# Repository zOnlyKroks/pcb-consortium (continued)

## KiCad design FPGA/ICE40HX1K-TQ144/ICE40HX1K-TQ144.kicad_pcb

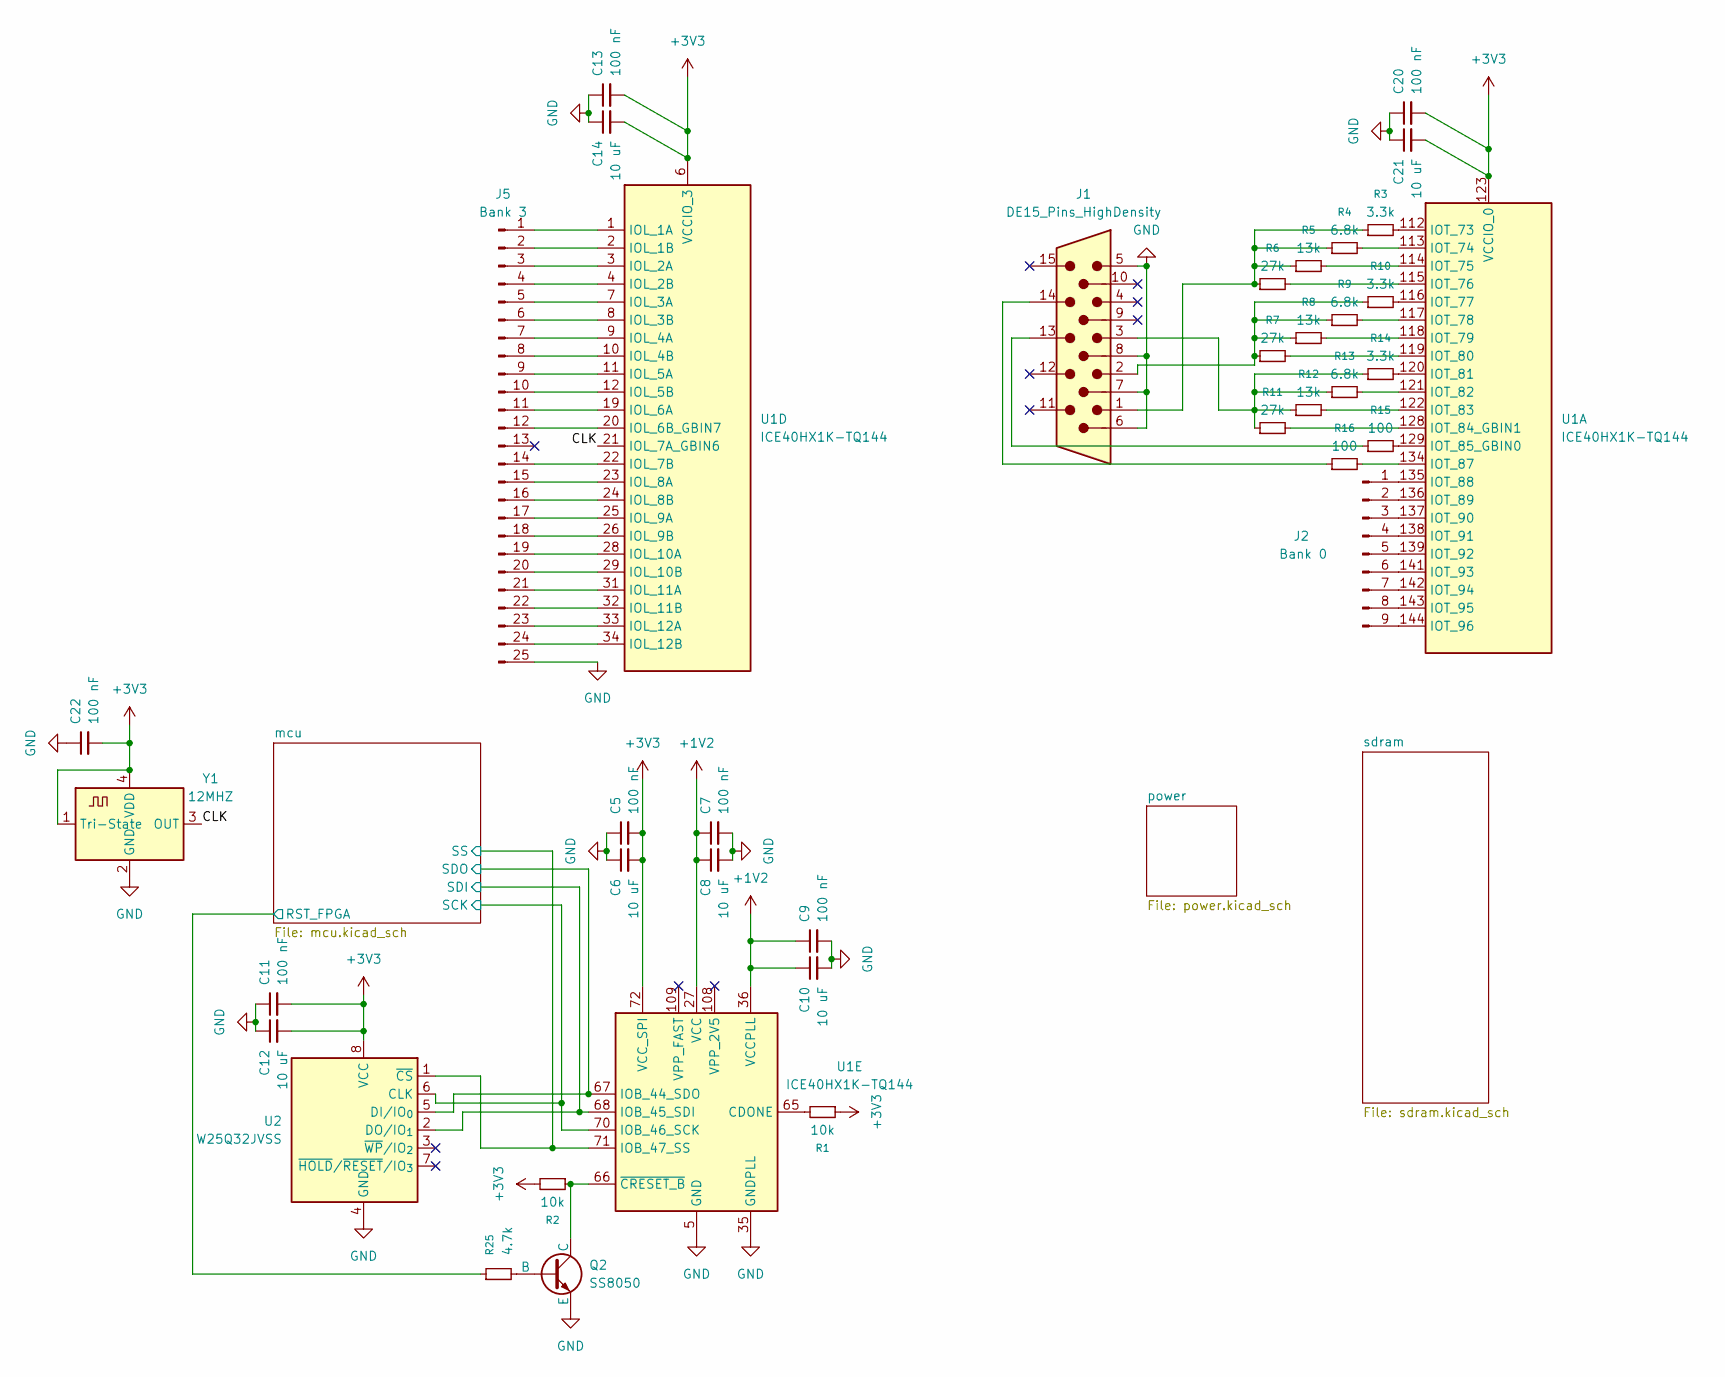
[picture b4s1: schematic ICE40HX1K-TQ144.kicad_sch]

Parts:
C5, C7, C9, C11, C13, C20, C22: 100 nF; C_0603_1608Metric
C6, C8, C10, C12, C14, C21: 10 uF; C_0603_1608Metric
J1: DE15_Pins_HighDensity; DSUB-15-HD_Pins_Horizontal_P2.29x1.90mm_EdgePinOffset3.03mm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
J2: Bank 0; PinHeader_1x09_P2.54mm_Vertical
J5: Bank 3; PinHeader_1x25_P2.54mm_Vertical
Q2: SS8050; SOT-23
R1, R2: 10k; R_0603_1608Metric
R3, R10, R14: 3.3k; R_0603_1608Metric
R4, R9, R13: 6.8k; R_0603_1608Metric
R5, R8, R12: 13k; R_0603_1608Metric
R6, R7, R11: 27k; R_0603_1608Metric
R15, R16: 100; R_0603_1608Metric
R25: 4.7k; R_0603_1608Metric; LCSC Part # C23162
U1: ICE40HX1K-TQ144; TQFP-144_20x20mm_P0.5mm
U2: W25Q32JVSS; SOIC-8_5.3x5.3mm_P1.27mm
Y1: 12MHZ; Crystal_SMD_3225-4Pin_3.2x2.5mm; LCSC Part # C2901561

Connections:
+1V2: C7.1, C8.1, C9.1, C10.1, U1.27 (VCC), U1.36 (VCCPLL), U1.51 (VCC), U1.92 (VCC), U1.111 (VCC); also elsewhere on the board
+3V3: C5.2, C6.2, C11.2, C12.2, C13.2, C14.2, C20.2, C21.2, C22.2, R1.1, R2.2, U1.6 (VCCIO_3), U1.30 (VCCIO_3), U1.72 (VCC_SPI), U1.123 (VCCIO_0), U1.133 (VCCIO_0), U2.8 (VCC), Y1.1 (Tri-State), Y1.4 (VDD); also elsewhere on the board
/CLK: U1.21 (IOL_7A_GBIN6), Y1.3 (OUT)
/mcu/RST_FPGA: R25.1; also elsewhere on the board
/mcu/SCK: U1.70 (IOB_46_SCK), U2.6 (CLK); also elsewhere on the board
/mcu/SDI: U1.68 (IOB_45_SDI), U2.2 (DO/IO_{1}); also elsewhere on the board
/mcu/SDO: U1.67 (IOB_44_SDO), U2.5 (DI/IO_{0}); also elsewhere on the board
/mcu/SS: U1.71 (IOB_47_SS), U2.1 (~CS); also elsewhere on the board
GND: C5.1, C6.1, C7.2, C8.2, C9.2, C10.2, C11.1, C12.1, C13.1, C14.1, C20.1, C21.1, C22.1, J1.5, J1.6, J1.7, J1.8, J5.25, Q2.3 (E), U1.5 (GND), U1.13 (GND), U1.14 (GND), U1.35 (GNDPLL), U1.59 (GND), U1.69 (GND), U1.86 (GND), U1.103 (GND), U1.132 (GND), U1.140 (GND), U2.4 (GND), Y1.2 (GND); also elsewhere on the board
unnamed: J1.1, R3.1, R4.1, R5.1, R6.1
unnamed: J1.2, R7.1, R8.1, R9.1, R10.1
unnamed: J1.3, R11.1, R12.1, R13.1, R14.1
unnamed: J1.13, R15.1
unnamed: J1.14, R16.1
unnamed: J2.1, U1.135 (IOT_88)
unnamed: J2.2, U1.136 (IOT_89)
unnamed: J2.3, U1.137 (IOT_90)
unnamed: J2.4, U1.138 (IOT_91)
unnamed: J2.5, U1.139 (IOT_92)
unnamed: J2.6, U1.141 (IOT_93)
unnamed: J2.7, U1.142 (IOT_94)
unnamed: J2.8, U1.143 (IOT_95)
unnamed: J2.9, U1.144 (IOT_96)
unnamed: J5.1, U1.1 (IOL_1A)
unnamed: J5.2, U1.2 (IOL_1B)
unnamed: J5.3, U1.3 (IOL_2A)
unnamed: J5.4, U1.4 (IOL_2B)
unnamed: J5.5, U1.7 (IOL_3A)
unnamed: J5.6, U1.8 (IOL_3B)
unnamed: J5.7, U1.9 (IOL_4A)
unnamed: J5.8, U1.10 (IOL_4B)
unnamed: J5.9, U1.11 (IOL_5A)
unnamed: J5.10, U1.12 (IOL_5B)
unnamed: J5.11, U1.19 (IOL_6A)
unnamed: J5.12, U1.20 (IOL_6B_GBIN7)
unnamed: J5.14, U1.22 (IOL_7B)
unnamed: J5.15, U1.23 (IOL_8A)
unnamed: J5.16, U1.24 (IOL_8B)
unnamed: J5.17, U1.25 (IOL_9A)
unnamed: J5.18, U1.26 (IOL_9B)
unnamed: J5.19, U1.28 (IOL_10A)
unnamed: J5.20, U1.29 (IOL_10B)
unnamed: J5.21, U1.31 (IOL_11A)
unnamed: J5.22, U1.32 (IOL_11B)
unnamed: J5.23, U1.33 (IOL_12A)
unnamed: J5.24, U1.34 (IOL_12B)
unnamed: Q2.2 (B), R25.2
unnamed: Q2.1 (C), R2.1, U1.66 (~CRESET_B)
unnamed: R3.2, U1.112 (IOT_73)
unnamed: R4.2, U1.113 (IOT_74)
unnamed: R5.2, U1.114 (IOT_75)
unnamed: R6.2, U1.115 (IOT_76)
unnamed: R10.2, U1.116 (IOT_77)
unnamed: R9.2, U1.117 (IOT_78)
unnamed: R8.2, U1.118 (IOT_79)
unnamed: R7.2, U1.119 (IOT_80)
unnamed: R14.2, U1.120 (IOT_81)
unnamed: R13.2, U1.121 (IOT_82)
unnamed: R12.2, U1.122 (IOT_83)
unnamed: R11.2, U1.128 (IOT_84_GBIN1)
unnamed: R15.2, U1.129 (IOT_85_GBIN0)
unnamed: R16.2, U1.134 (IOT_87)
unnamed: R1.2, U1.65 (CDONE)

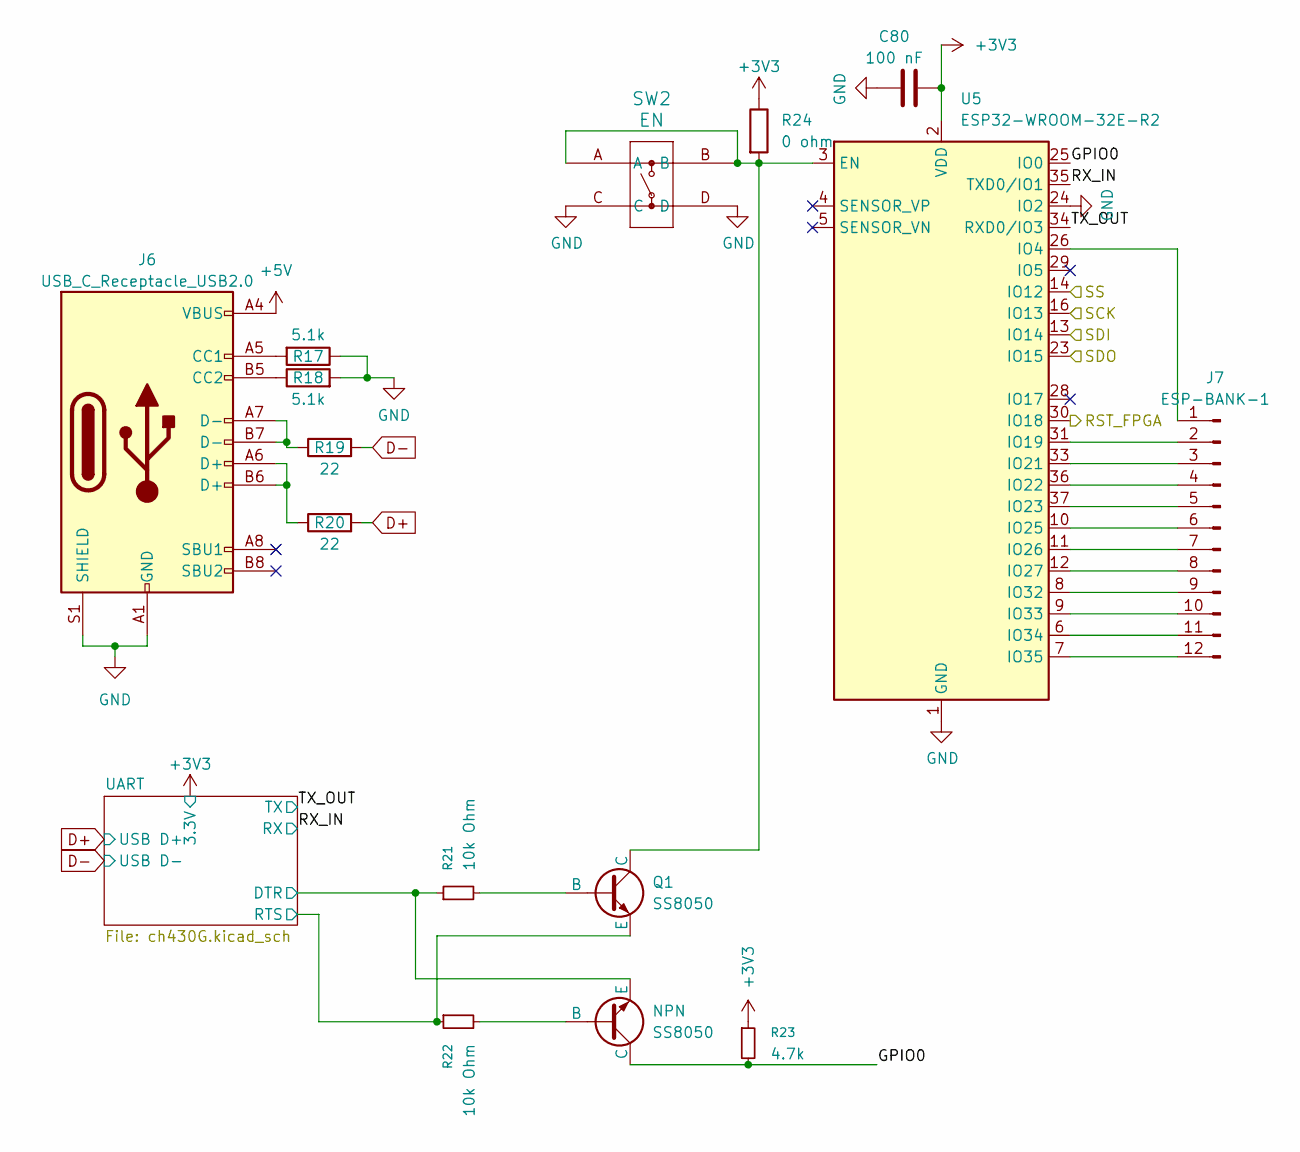
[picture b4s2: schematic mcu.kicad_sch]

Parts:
C80: 100 nF; C_0805_2012Metric; LCSC Part # C49678
J6: USB_C_Receptacle_USB2.0; USB_C_Receptacle_HRO_TYPE-C-31-M-12; JlcRotOffset 180
J7: ESP-BANK-1; PinHeader_1x12_P2.54mm_Vertical
Q1: SS8050; SOT-23
R17, R18: 5.1k; R_0805_2012Metric; LCSC Part # C27834
R19, R20: 22; R_0805_2012Metric; LCSC Part # C17561
R21, R22: 10k Ohm; R_0805_2012Metric
R23: 4.7k; R_0603_1608Metric; LCSC Part # C23162
R24: 0 ohm; R_0805_2012Metric; LCSC Part # C17477
SS8050: NPN; SOT-23
SW2: EN; KH-6X6X5H-STM_SKE; LCSC Part # C2837531
U5: ESP32-WROOM-32E-R2; ESP32-WROOM-32D

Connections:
+3V3: C80.1, R23.1, R24.1, U5.2 (VDD); also elsewhere on the board
+5V: J6.A4 (VBUS), J6.A9 (VBUS), J6.B4 (VBUS), J6.B9 (VBUS); also elsewhere on the board
/mcu/GPIO0: R23.2, SS8050.1 (C), U5.25 (IO0)
/mcu/RST_FPGA: U5.30 (IO18); also elsewhere on the board
/mcu/RX_IN: U5.35 (TXD0/IO1); also elsewhere on the board
/mcu/SCK: U5.16 (IO13); also elsewhere on the board
/mcu/SDI: U5.13 (IO14); also elsewhere on the board
/mcu/SDO: U5.23 (IO15); also elsewhere on the board
/mcu/SS: U5.14 (IO12); also elsewhere on the board
/mcu/TX_OUT: U5.34 (RXD0/IO3); also elsewhere on the board
/mcu/UART/DTR: R21.1, SS8050.3 (E); also elsewhere on the board
/mcu/UART/RTS: Q1.3 (E), R22.1; also elsewhere on the board
D+: R20.2; also elsewhere on the board
D-: R19.2; also elsewhere on the board
GND: C80.2, J6.A1 (GND), J6.A12 (GND), J6.B1 (GND), J6.B12 (GND), J6.S1 (SHIELD), R17.1, R18.2, SW2.C, SW2.D, U5.1 (GND), U5.15 (GND), U5.24 (IO2), U5.38 (GND), U5.39 (GND); also elsewhere on the board
unnamed: J6.A5 (CC1), R17.2
unnamed: J6.B5 (CC2), R18.1
unnamed: J6.A6 (D+), J6.B6 (D+), R20.1
unnamed: J6.A7 (D-), J6.B7 (D-), R19.1
unnamed: J7.1, U5.26 (IO4)
unnamed: J7.2, U5.31 (IO19)
unnamed: J7.3, U5.33 (IO21)
unnamed: J7.4, U5.36 (IO22)
unnamed: J7.5, U5.37 (IO23)
unnamed: J7.6, U5.10 (IO25)
unnamed: J7.7, U5.11 (IO26)
unnamed: J7.8, U5.12 (IO27)
unnamed: J7.9, U5.8 (IO32)
unnamed: J7.10, U5.9 (IO33)
unnamed: J7.11, U5.6 (IO34)
unnamed: J7.12, U5.7 (IO35)
unnamed: Q1.2 (B), R21.2
unnamed: Q1.1 (C), R24.2, SW2.A, SW2.B, U5.3 (EN)
unnamed: R22.2, SS8050.2 (B)

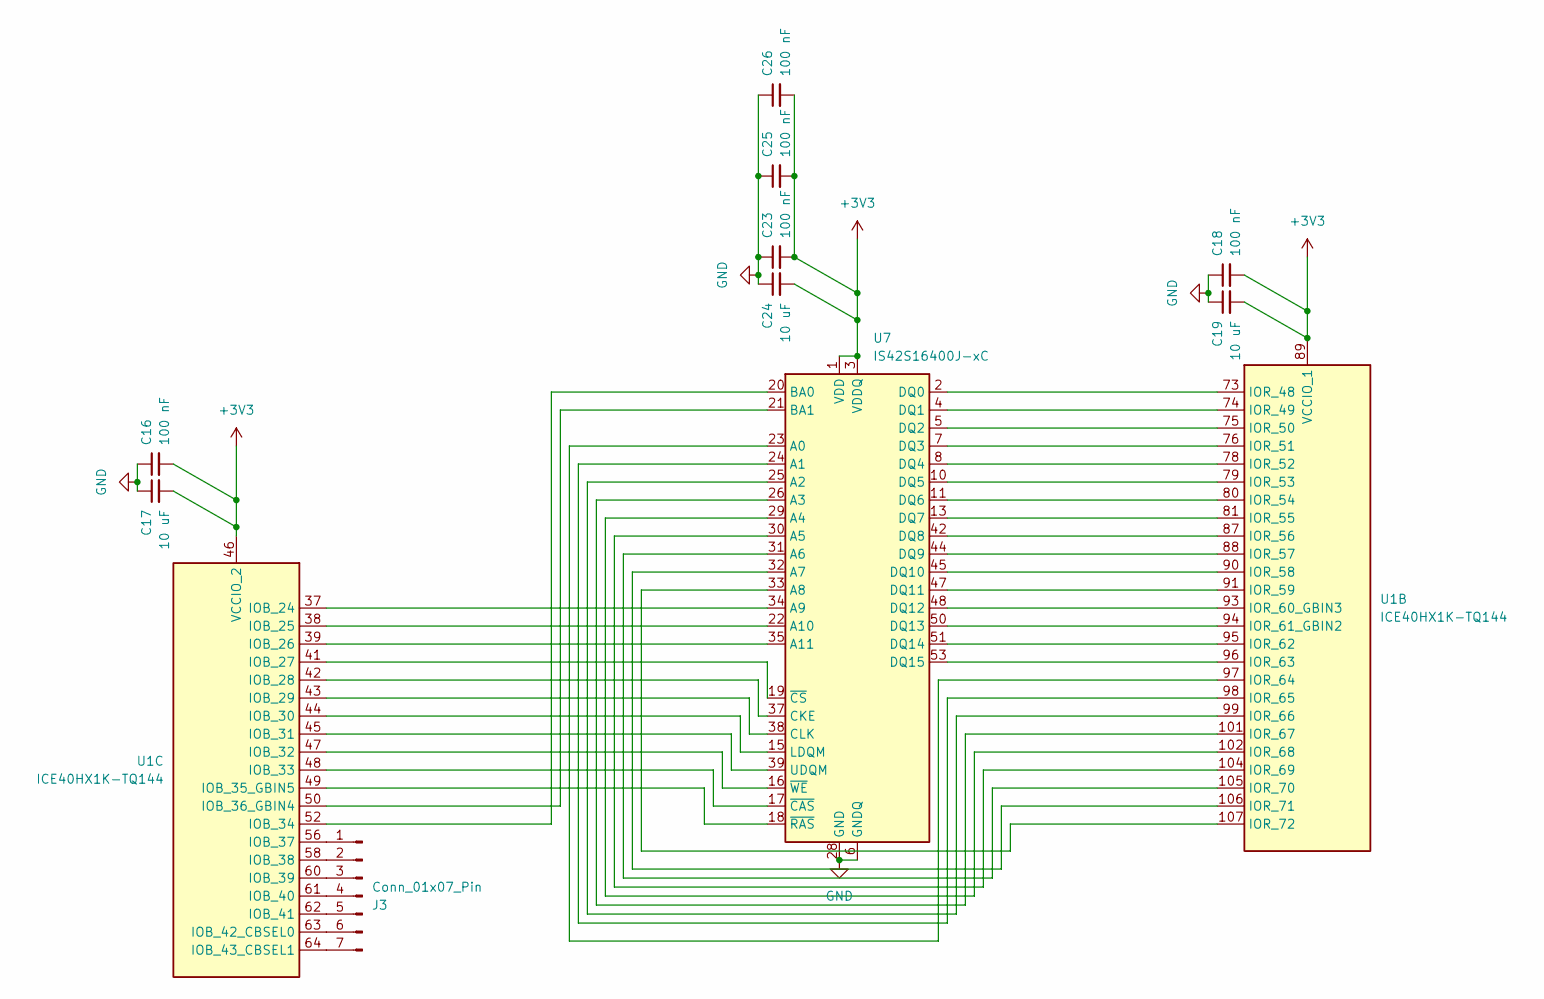
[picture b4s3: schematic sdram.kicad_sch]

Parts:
C16, C18, C23, C25, C26: 100 nF; C_0603_1608Metric
C17, C19, C24: 10 uF; C_0603_1608Metric
J3: Conn_01x07_Pin; PinHeader_1x07_P2.54mm_Vertical
U1: ICE40HX1K-TQ144; TQFP-144_20x20mm_P0.5mm
U7: IS42S16400J-xC; TSOP-II-54_22.2x10.16mm_P0.8mm

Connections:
+3V3: C16.2, C17.2, C18.2, C19.2, C23.2, C24.2, C25.2, C26.2, U1.46 (VCCIO_2), U1.57 (VCCIO_2), U1.89 (VCCIO_1), U1.100 (VCCIO_1), U7.1 (VDD), U7.3 (VDDQ), U7.9 (VDDQ), U7.14 (VDD), U7.27 (VDD), U7.43 (VDDQ), U7.49 (VDDQ); also elsewhere on the board
GND: C16.1, C17.1, C18.1, C19.1, C23.1, C24.1, C25.1, C26.1, U7.6 (GNDQ), U7.12 (GNDQ), U7.28 (GND), U7.41 (GND), U7.46 (GNDQ), U7.52 (GNDQ), U7.54 (GND); also elsewhere on the board
unnamed: J3.1, U1.56 (IOB_37)
unnamed: J3.2, U1.58 (IOB_38)
unnamed: J3.3, U1.60 (IOB_39)
unnamed: J3.4, U1.61 (IOB_40)
unnamed: J3.5, U1.62 (IOB_41)
unnamed: J3.6, U1.63 (IOB_42_CBSEL0)
unnamed: J3.7, U1.64 (IOB_43_CBSEL1)
unnamed: U1.73 (IOR_48), U7.2 (DQ0)
unnamed: U1.74 (IOR_49), U7.4 (DQ1)
unnamed: U1.75 (IOR_50), U7.5 (DQ2)
unnamed: U1.76 (IOR_51), U7.7 (DQ3)
unnamed: U1.78 (IOR_52), U7.8 (DQ4)
unnamed: U1.79 (IOR_53), U7.10 (DQ5)
unnamed: U1.80 (IOR_54), U7.11 (DQ6)
unnamed: U1.81 (IOR_55), U7.13 (DQ7)
unnamed: U1.87 (IOR_56), U7.42 (DQ8)
unnamed: U1.88 (IOR_57), U7.44 (DQ9)
unnamed: U1.90 (IOR_58), U7.45 (DQ10)
unnamed: U1.91 (IOR_59), U7.47 (DQ11)
unnamed: U1.93 (IOR_60_GBIN3), U7.48 (DQ12)
unnamed: U1.94 (IOR_61_GBIN2), U7.50 (DQ13)
unnamed: U1.95 (IOR_62), U7.51 (DQ14)
unnamed: U1.96 (IOR_63), U7.53 (DQ15)
unnamed: U1.97 (IOR_64), U7.23 (A0)
unnamed: U1.98 (IOR_65), U7.24 (A1)
unnamed: U1.99 (IOR_66), U7.25 (A2)
unnamed: U1.101 (IOR_67), U7.26 (A3)
unnamed: U1.102 (IOR_68), U7.29 (A4)
unnamed: U1.104 (IOR_69), U7.30 (A5)
unnamed: U1.105 (IOR_70), U7.31 (A6)
unnamed: U1.106 (IOR_71), U7.32 (A7)
unnamed: U1.107 (IOR_72), U7.33 (A8)
unnamed: U1.37 (IOB_24), U7.34 (A9)
unnamed: U1.38 (IOB_25), U7.22 (A10)
unnamed: U1.39 (IOB_26), U7.35 (A11)
unnamed: U1.41 (IOB_27), U7.19 (~CS)
unnamed: U1.42 (IOB_28), U7.37 (CKE)
unnamed: U1.43 (IOB_29), U7.38 (CLK)
unnamed: U1.44 (IOB_30), U7.15 (LDQM)
unnamed: U1.45 (IOB_31), U7.39 (UDQM)
unnamed: U1.47 (IOB_32), U7.16 (~WE)
unnamed: U1.48 (IOB_33), U7.17 (~CAS)
unnamed: U1.52 (IOB_34), U7.20 (BA0)
unnamed: U1.49 (IOB_35_GBIN5), U7.18 (~RAS)
unnamed: U1.50 (IOB_36_GBIN4), U7.21 (BA1)

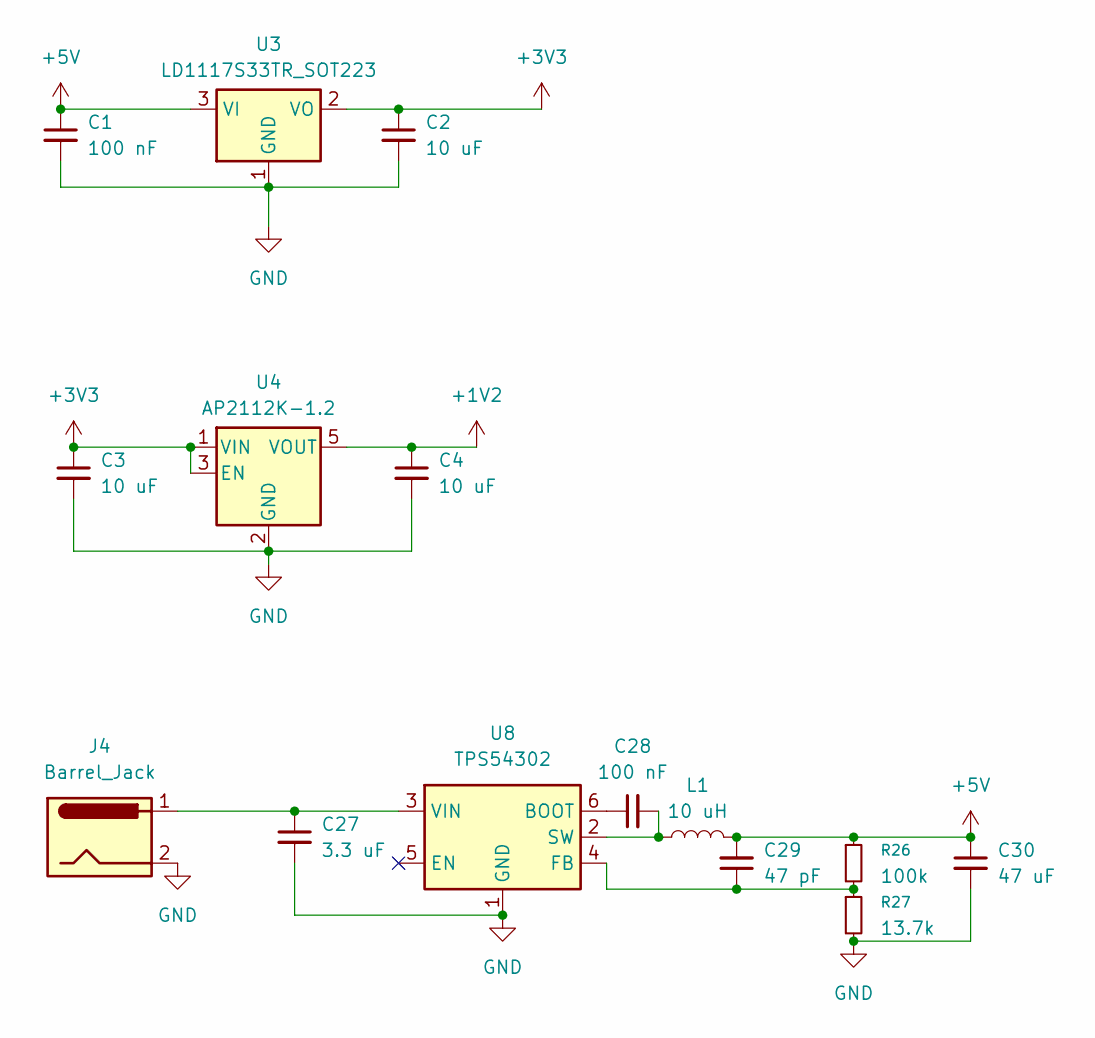
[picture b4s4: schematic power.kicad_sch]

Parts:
C1, C28: 100 nF; C_0603_1608Metric
C2, C3, C4: 10 uF; C_0603_1608Metric
C27: 3.3 uF; C_0603_1608Metric
C29: 47 pF; C_0603_1608Metric
C30: 47 uF; C_0603_1608Metric
J4: Barrel_Jack; BarrelJack_Horizontal
L1: 10 uH; L_0805_2012Metric
R26: 100k; R_0603_1608Metric
R27: 13.7k; R_0603_1608Metric
U3: LD1117S33TR_SOT223; SOT-223-3_TabPin2
U4: AP2112K-1.2; SOT-23-5
U8: TPS54302; SOT-23-6

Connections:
+1V2: C4.1, U4.5 (VOUT); also elsewhere on the board
+3V3: C2.1, C3.1, U3.2 (VO), U4.1 (VIN), U4.3 (EN); also elsewhere on the board
+5V: C1.1, C29.2, C30.1, L1.2, R26.1, U3.3 (VI); also elsewhere on the board
GND: C1.2, C2.2, C3.2, C4.2, C27.2, C30.2, J4.2, R27.2, U3.1 (GND), U4.2 (GND), U8.1 (GND); also elsewhere on the board
unnamed: C28.1, U8.6 (BOOT)
unnamed: C29.1, R26.2, R27.1, U8.4 (FB)
unnamed: C28.2, L1.1, U8.2 (SW)
unnamed: C27.1, J4.1, U8.3 (VIN)

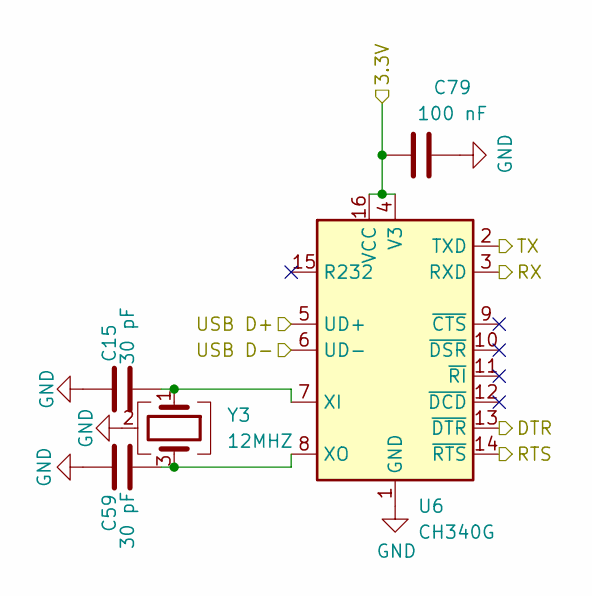
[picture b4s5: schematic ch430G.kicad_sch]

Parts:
C15, C59: 30 pF; C_0805_2012Metric; LCSC Part # C107108
C79: 100 nF; C_0805_2012Metric; LCSC Part # C49678
U6: CH340G; SOIC-16_3.9x9.9mm_P1.27mm
Y3: 12MHZ; Crystal_SMD_3225-4Pin_3.2x2.5mm; LCSC Part # C19631429

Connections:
+3V3: C79.2, U6.4 (V3), U6.16 (VCC); also elsewhere on the board
/mcu/RX_IN: U6.3 (RXD); also elsewhere on the board
/mcu/TX_OUT: U6.2 (TXD); also elsewhere on the board
/mcu/UART/DTR: U6.13 (~DTR); also elsewhere on the board
/mcu/UART/RTS: U6.14 (~RTS); also elsewhere on the board
D+: U6.5 (UD+); also elsewhere on the board
D-: U6.6 (UD-); also elsewhere on the board
GND: C15.1, C59.1, C79.1, U6.1 (GND), Y3.2 (G), Y3.4 (G); also elsewhere on the board
unnamed: C15.2, U6.7 (XI), Y3.1
unnamed: C59.2, U6.8 (XO), Y3.3

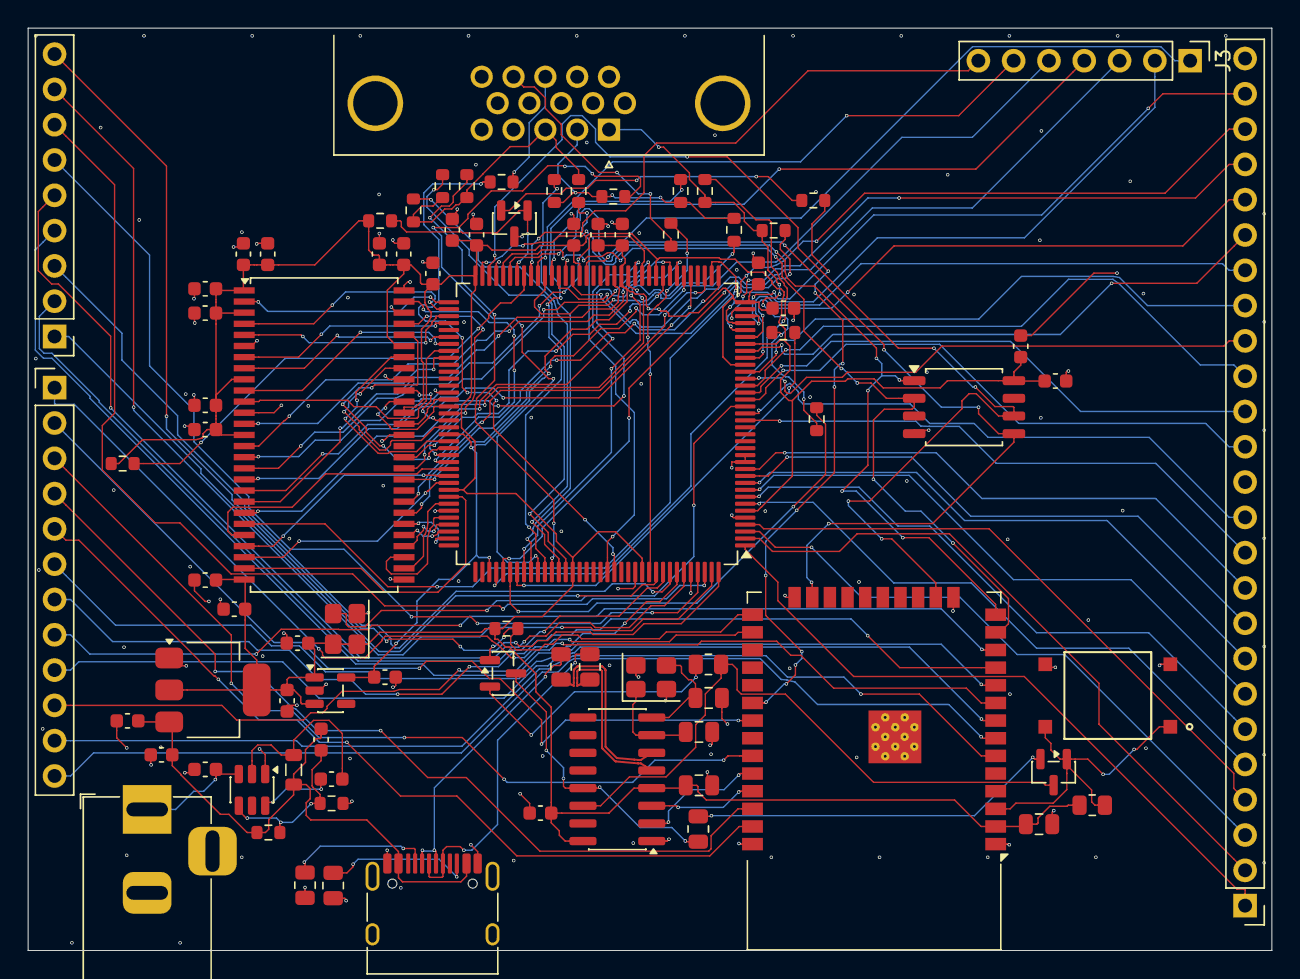
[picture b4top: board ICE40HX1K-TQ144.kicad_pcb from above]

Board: 4 copper layers, 89.5 x 66.4 mm, 82 parts (0 on the bottom side), 141 nets.

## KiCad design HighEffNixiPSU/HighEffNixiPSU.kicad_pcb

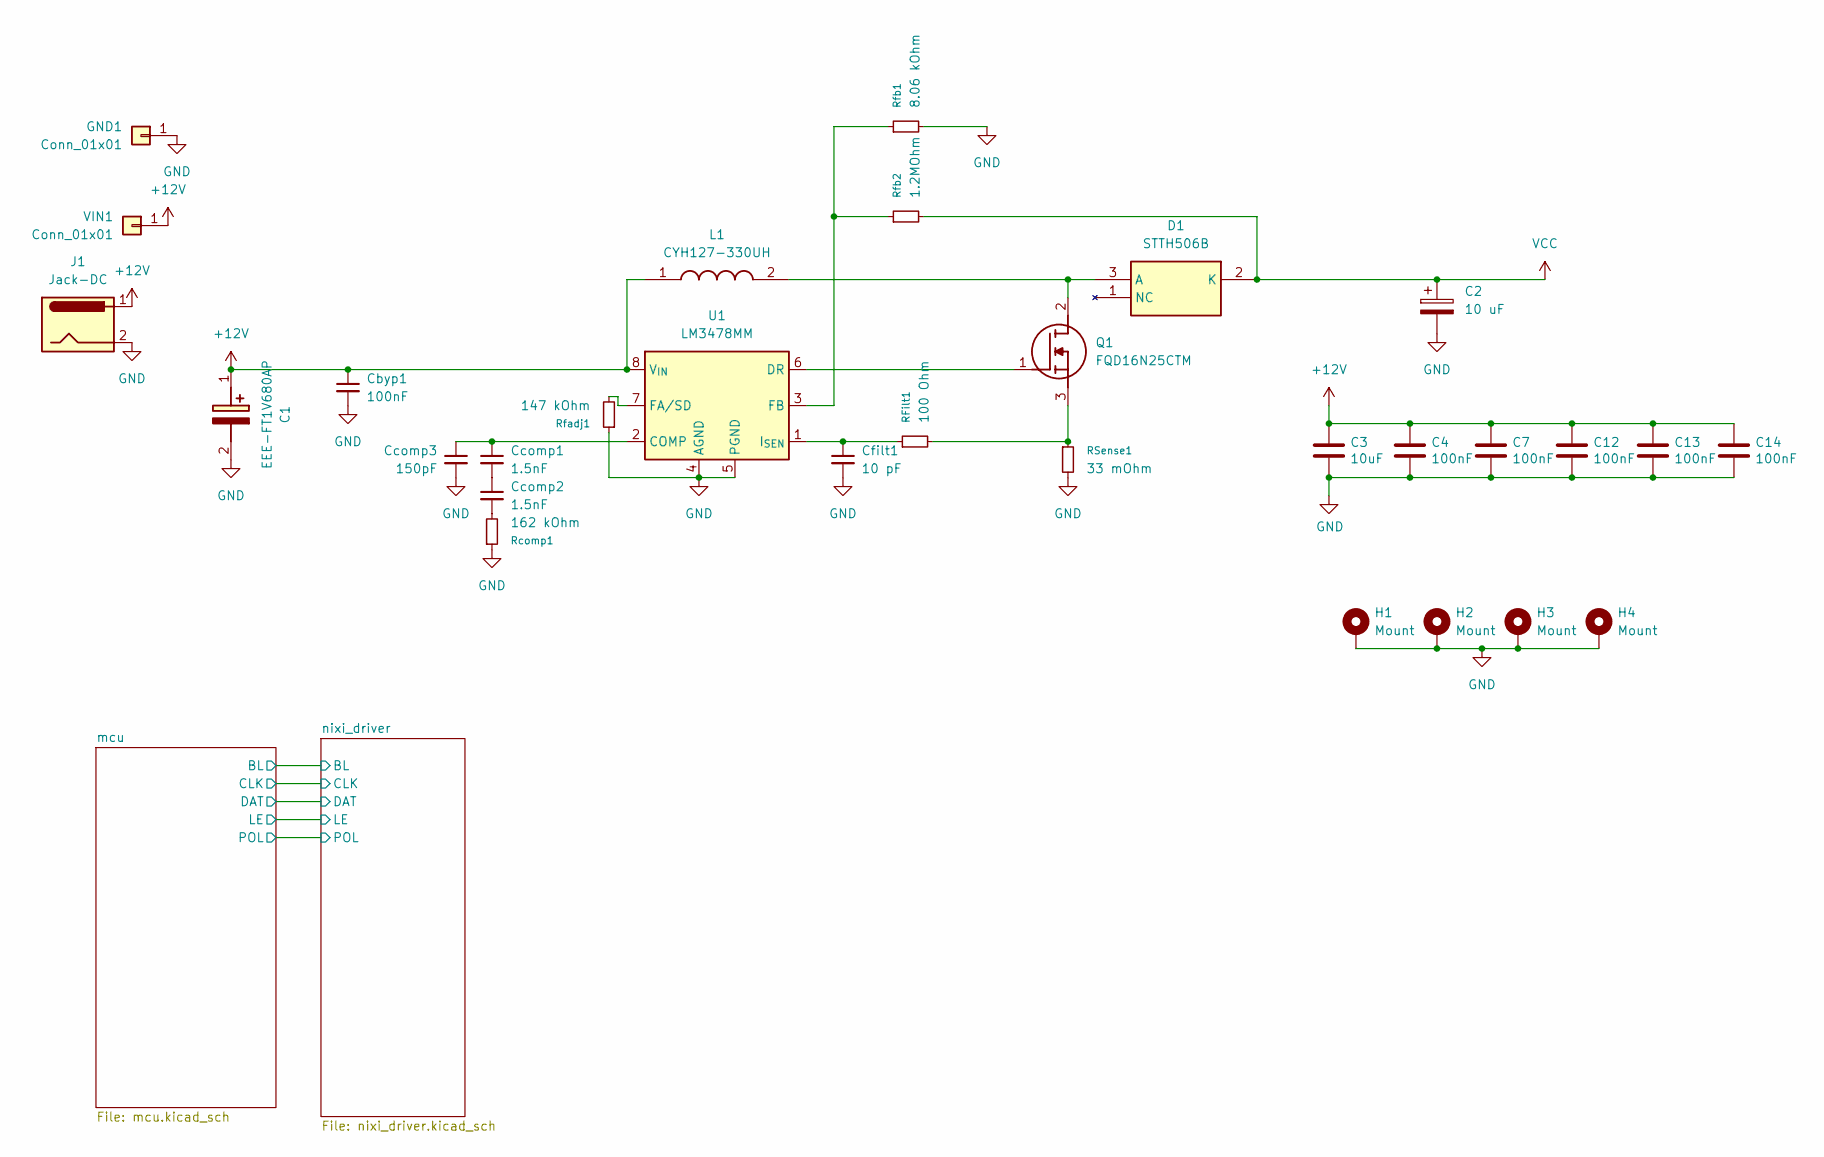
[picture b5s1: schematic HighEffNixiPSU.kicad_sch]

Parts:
C1: EEE-FT1V680AP; EEE1AA101SP; Mouser Part Number 667-EEE-FT1V680AP
C2: 10 uF; C_Elec_10x10.2; LCSC Part # C48970948
C3: 10uF; C_0805_2012Metric; LCSC C15850
C4, C7, C12, C13, C14: 100nF; C_0805_2012Metric; LCSC C28233
Cbyp1: 100nF; C_0805_2012Metric; LCSC Part # C784084
Ccomp1, Ccomp2: 1.5nF; C_0805_2012Metric; LCSC Part # C1717
Ccomp3: 150pF; C_0805_2012Metric; LCSC Part # C2168780
Cfilt1: 10 pF; C_0805_2012Metric; LCSC Part # C107107
D1: STTH506B; STTH506BTR; Mouser Part Number 511-STTH506B-TR
GND1: Conn_01x01; PinHeader_1x01_P2.54mm_Vertical; LCSC Part # C492400
H1, H2, H3, H4: Mount; MountingHole_3mm_Pad_TopOnly
J1: Jack-DC; BarrelJack_CUI_PJ-063AH_Horizontal; LCSC Part # C22434582
L1: CYH127-330UH; Mouser Part Number 652-SDR1307-331KL
Q1: FQD16N25CTM; Mouser Part Number 512-FQD16N25CTM
RFilt1: 100 Ohm; R_0805_2012Metric; LCSC Part # C17408
RSense1: 33 mOhm; R_1210_3225Metric; LCSC Part # C723419
Rcomp1: 162 kOhm; R_0805_2012Metric; LCSC Part # C47115899
Rfadj1: 147 kOhm; R_0805_2012Metric; LCSC Part # C47115874
Rfb1: 8.06 kOhm; R_0805_2012Metric; LCSC Part # C857074
Rfb2: 1.2MOhm; R_1206_3216Metric; LCSC Part # C36337
U1: LM3478MM; VSSOP-8_3x3mm_P0.65mm; LCSC Part # C9404
VIN1: Conn_01x01; PinHeader_1x01_P2.54mm_Vertical; LCSC Part # C492400

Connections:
+12V: C1.1 (+), C3.1, C4.1, C7.1, C12.1, C13.1, C14.1, Cbyp1.1, J1.1, L1.1, U1.8 (V_{IN}), VIN1.1; also elsewhere on the board
GND: C1.2 (-), C2.2, C3.2, C4.2, C7.2, C12.2, C13.2, C14.2, Cbyp1.2, Ccomp3.2, Cfilt1.2, GND1.1, H1.1, H2.1, H3.1, H4.1, J1.2, RSense1.2, Rcomp1.1, Rfadj1.1, Rfb1.2, U1.4 (AGND), U1.5 (PGND); also elsewhere on the board
unnamed: Ccomp1.2, Ccomp2.1
unnamed: Ccomp2.2, Rcomp1.2
unnamed: D1.3 (A), L1.2, Q1.2 (D)
unnamed: Q1.1 (G), U1.6 (DR)
unnamed: Q1.3 (S), RFilt1.2, RSense1.1
unnamed: Ccomp1.1, Ccomp3.1, U1.2 (COMP)
unnamed: Rfadj1.2, U1.7 (FA/SD)
unnamed: Rfb1.1, Rfb2.1, U1.3 (FB)
unnamed: Cfilt1.1, RFilt1.1, U1.1 (I_{SEN})
VCC: C2.1, D1.2 (K), Rfb2.2; also elsewhere on the board

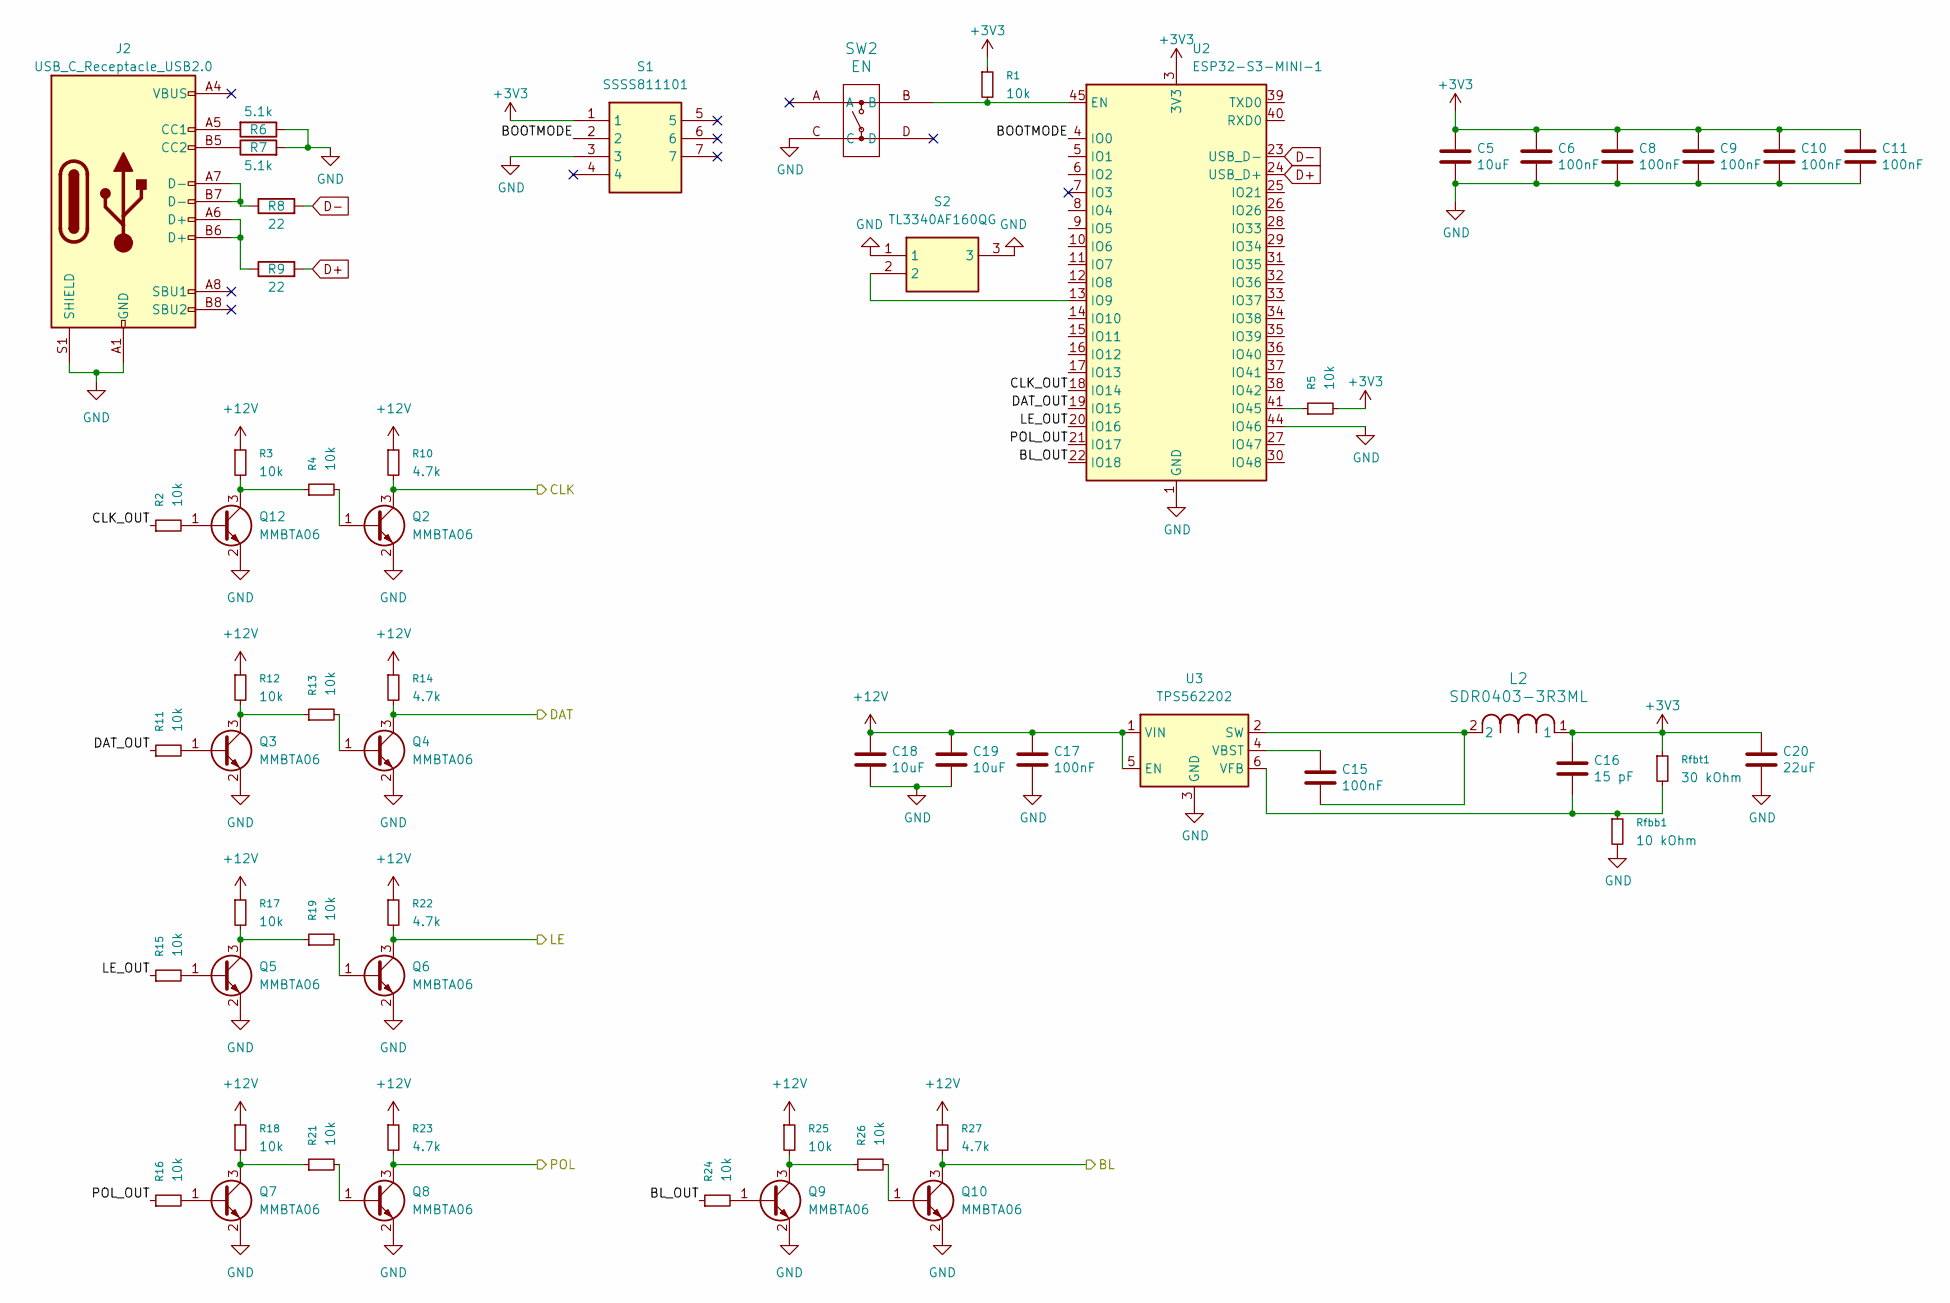
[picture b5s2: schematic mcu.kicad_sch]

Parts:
C5: 10uF; C_0805_2012Metric; LCSC C15850
C6, C8, C9, C10, C11: 100nF; C_0805_2012Metric; LCSC C28233
C15, C17: 100nF; C_0603_1608Metric; LCSC C22401913
C16: 15 pF; C_0402_1005Metric; LCSC C22401913
C18, C19: 10uF; C_0805_2012Metric; LCSC C6684487
C20: 22uF; C_0805_2012Metric; LCSC C441864
J2: USB_C_Receptacle_USB2.0; USB_C_Receptacle_HRO_TYPE-C-31-M-12; JlcRotOffset 180
L2: SDR0403-3R3ML; IND_BOURNS_SDR0403; LCSC Part # C139481
Q2, Q3, Q4, Q5, Q6, Q7, Q8, Q9, Q10, Q12: MMBTA06; SOT-23; LCSC Part # C20069139
R1, R2, R3, R4, R5, R11, R12, R13, R15, R16, R17, R18, R19, R21, R24, R25, R26: 10k; R_0805_2012Metric; LCSC Part # C17414
R6, R7: 5.1k; R_0805_2012Metric; LCSC Part # C27834
R8, R9: 22; R_0805_2012Metric; LCSC Part # C17561
R10, R14, R22, R23, R27: 4.7k; R_0805_2012Metric; LCSC Part # C17673
Rfbb1: 10 kOhm; R_0603_1608Metric; LCSC Part # C98220
Rfbt1: 30 kOhm; R_0805_2012Metric; LCSC Part # C2907255
S1: SSSS811101; Mouser Part Number 688-SSSS811101
S2: TL3340AF160QG; TL3340; Mouser Part Number 612-TL3340AF160QG
SW2: EN; KH-6X6X5H-STM_SKE; LCSC Part # C2837531
U2: ESP32-S3-MINI-1; ESP32-S2-MINI-1; LCSC Part # C2913206
U3: TPS562202; SOT-563

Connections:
+3V3: C5.1, C6.1, C8.1, C9.1, C10.1, C11.1, C16.1, C20.1, L2.1, R1.1, R5.2, Rfbt1.1, S1.1, U2.3 (3V3)
+12V: C17.1, C18.1, C19.1, R3.1, R10.1, R12.1, R14.1, R17.1, R18.1, R22.1, R23.1, R25.1, R27.1, U3.1 (VIN), U3.5 (EN); also elsewhere on the board
/mcu/BL: Q10.3 (C), R27.2; also elsewhere on the board
/mcu/BL_OUT: R24.1, U2.22 (IO18)
/mcu/BOOTMODE: S1.2, U2.4 (IO0)
/mcu/CLK: Q2.3 (C), R10.2; also elsewhere on the board
/mcu/CLK_OUT: R2.1, U2.18 (IO14)
/mcu/DAT: Q4.3 (C), R14.2; also elsewhere on the board
/mcu/DAT_OUT: R11.1, U2.19 (IO15)
/mcu/LE: Q6.3 (C), R22.2; also elsewhere on the board
/mcu/LE_OUT: R15.1, U2.20 (IO16)
/mcu/POL: Q8.3 (C), R23.2; also elsewhere on the board
/mcu/POL_OUT: R16.1, U2.21 (IO17)
D+: R9.2, U2.24 (USB_D+)
D-: R8.2, U2.23 (USB_D-)
GND: C5.2, C6.2, C8.2, C9.2, C10.2, C11.2, C17.2, C18.2, C19.2, C20.2, J2.A1 (GND), J2.A12 (GND), J2.B1 (GND), J2.B12 (GND), J2.S1 (SHIELD), Q2.2 (E), Q3.2 (E), Q4.2 (E), Q5.2 (E), Q6.2 (E), Q7.2 (E), Q8.2 (E), Q9.2 (E), Q10.2 (E), Q12.2 (E), R6.1, R7.2, Rfbb1.2, S1.3, S2.1, S2.3, SW2.C, U2.1 (GND), U2.2 (GND), U2.42 (GND), U2.43 (GND), U2.44 (IO46), U2.46 (GND), U2.47 (GND), U2.48 (GND), U2.49 (GND), U2.50 (GND), U2.51 (GND), U2.52 (GND), U2.53 (GND), U2.54 (GND), U2.55 (GND), U2.56 (GND), U2.57 (GND), U2.58 (GND), U2.59 (GND), U2.60 (GND), U2.61 (GND), U2.62 (GND), U2.63 (GND), U2.64 (GND), U2.65 (GND), U3.3 (GND); also elsewhere on the board
unnamed: J2.A5 (CC1), R6.2
unnamed: J2.B5 (CC2), R7.1
unnamed: J2.A6 (D+), J2.B6 (D+), R9.1
unnamed: J2.A7 (D-), J2.B7 (D-), R8.1
unnamed: Q2.1 (B), R4.2
unnamed: Q3.1 (B), R11.2
unnamed: Q3.3 (C), R12.2, R13.1
unnamed: Q4.1 (B), R13.2
unnamed: Q5.1 (B), R15.2
unnamed: Q5.3 (C), R17.2, R19.1
unnamed: Q6.1 (B), R19.2
unnamed: Q7.1 (B), R16.2
unnamed: Q7.3 (C), R18.2, R21.1
unnamed: Q8.1 (B), R21.2
unnamed: Q9.1 (B), R24.2
unnamed: Q9.3 (C), R25.2, R26.1
unnamed: Q10.1 (B), R26.2
unnamed: Q12.1 (B), R2.2
unnamed: Q12.3 (C), R3.2, R4.1
unnamed: R1.2, SW2.B, U2.45 (EN)
unnamed: S2.2, U2.13 (IO9)
unnamed: R5.1, U2.41 (IO45)
unnamed: C15.2, L2.2, U3.2 (SW)
unnamed: C15.1, U3.4 (VBST)
unnamed: C16.2, Rfbb1.1, Rfbt1.2, U3.6 (VFB)
